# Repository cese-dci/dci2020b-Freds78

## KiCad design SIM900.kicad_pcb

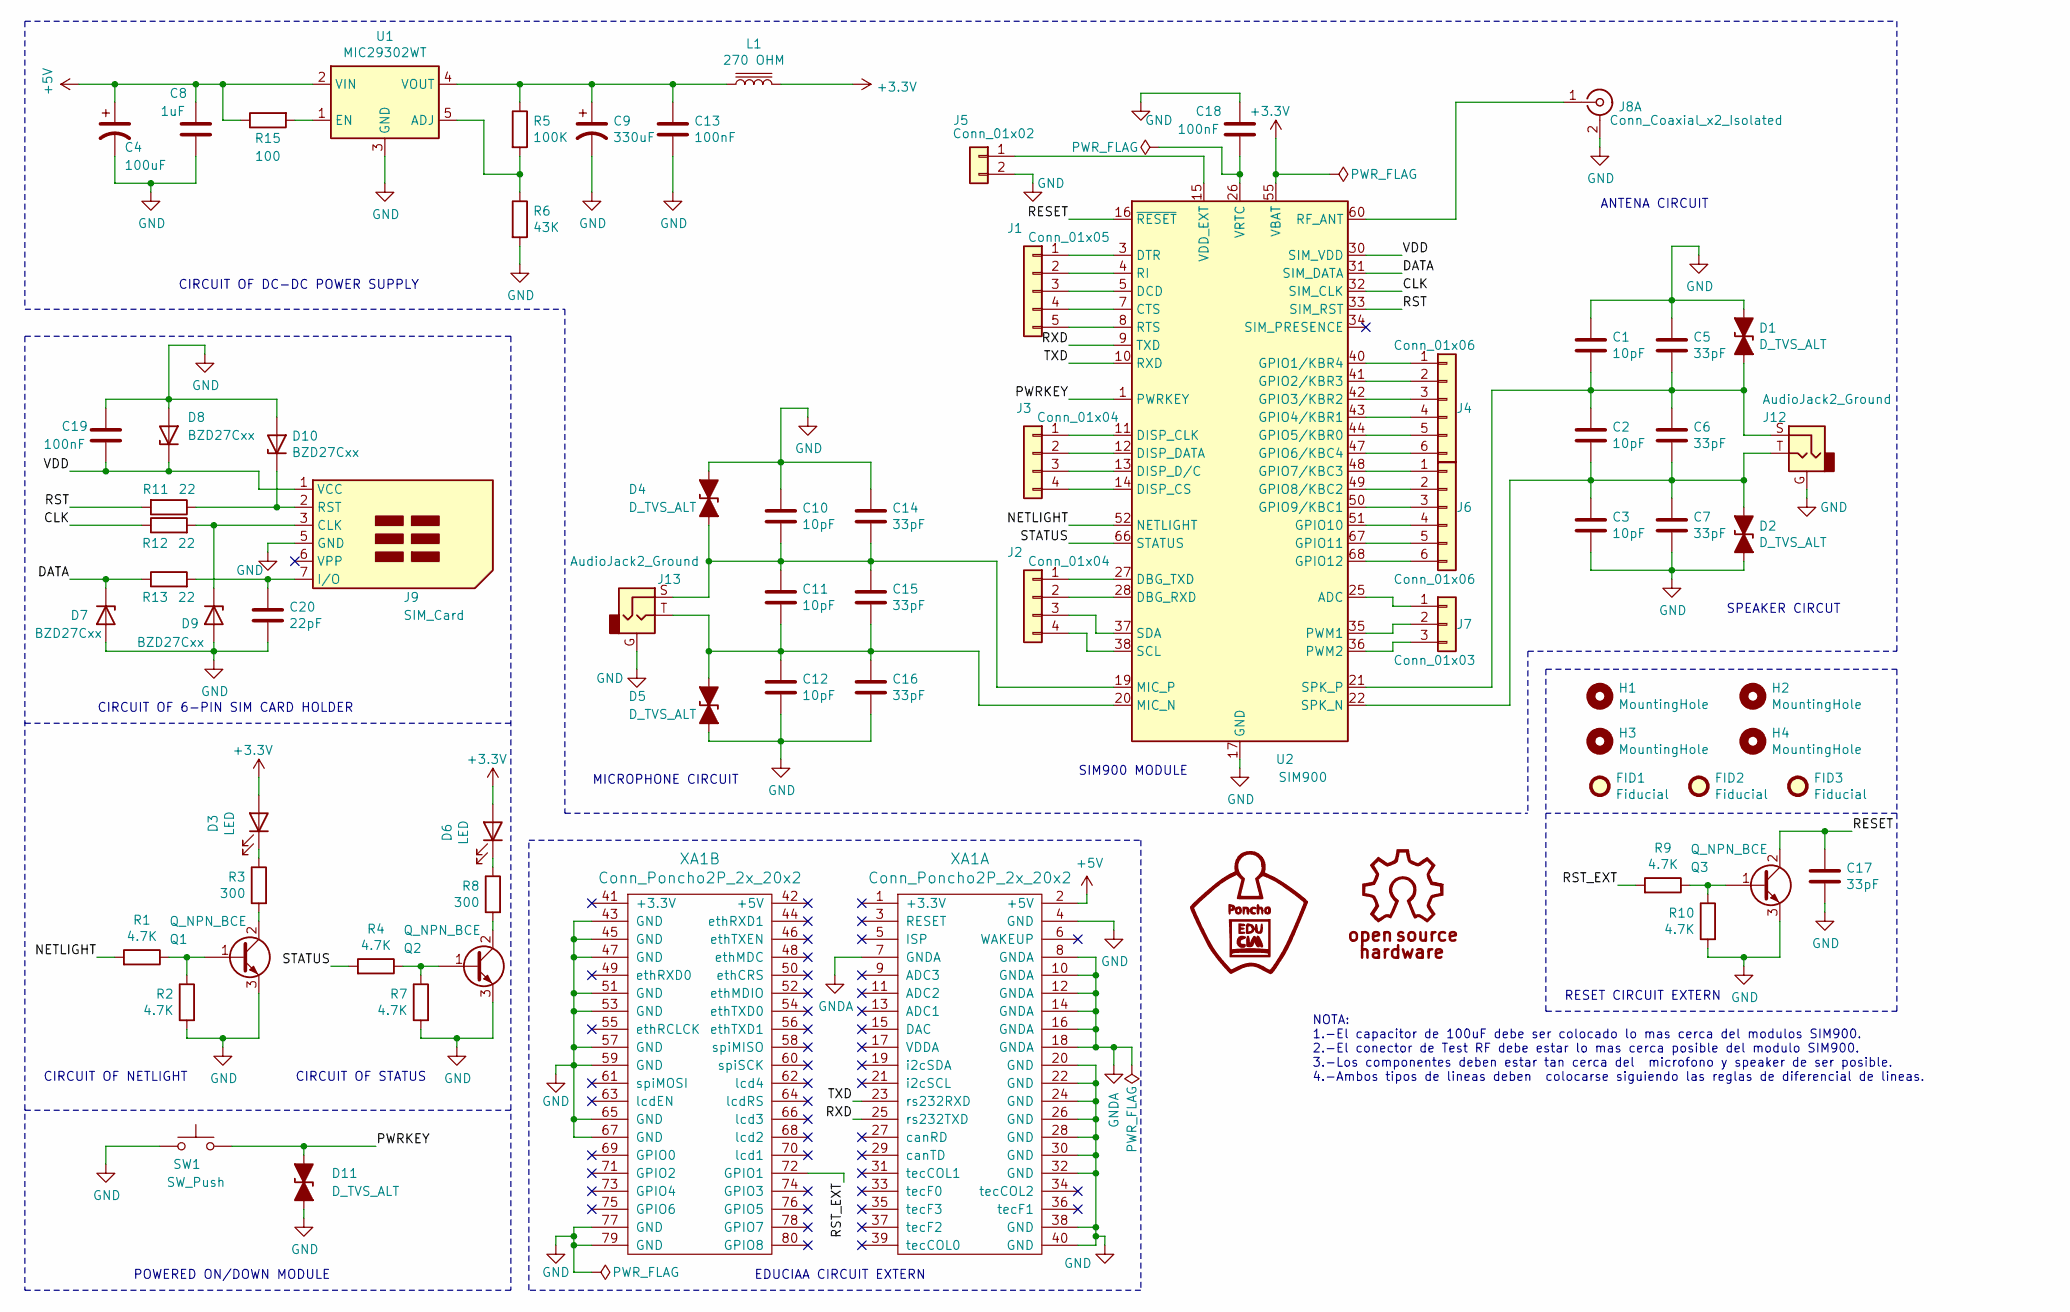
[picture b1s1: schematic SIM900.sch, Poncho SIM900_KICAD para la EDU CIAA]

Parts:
C1, C2, C3, C10, C11, C12: 10pF; C_0805_2012Metric; Digikey 399-17617-2-ND
C4: 100uF; C_1206_3216Metric; Digikey 718-2364-6-ND
C5, C6, C7, C14, C15, C16, C17: 33pF; C_0805_2012Metric; Digikey 399-17617-2-ND
C8: 1uF; C_0805_2012Metric; Digikey 399-17617-2-ND
C9: 330uF; C_2312_2020Metric_Pad3.2x6.0mm_HandSolder
C13, C18, C19: 100nF; C_0805_2012Metric; Digikey 399-17617-2-ND
C20: 22pF; C_0805_2012Metric; Digikey 399-17617-2-ND
D1, D2, D4, D11: D_TVS_ALT; D_SMA_Handsoldering; Digikey SMAJ22CAQ-13-FDITR-ND
D3: LED; LED_0805_2012Metric; Digikey 2460-L171L-QYC-TR-ND
D5: D_TVS_ALT; D_SMA_Handsoldering
D6: LED; LED_0805_2012Metric; Digikey 2460-L171L-LICTR-ND
D7: BZD27Cxx; D_SMF
D8, D9, D10: BZD27Cxx; D_SMF; Digikey BZD27C16P-E3-08GITR-ND
FID1, FID2, FID3: Fiducial; Fiducial_0.75mm_Mask2.25mm
H1, H2, H3, H4: MountingHole; MountingHole_2.5mm_Pad
J1: Conn_01x05; PinHeader_1x05_P2.54mm_Vertical; Digikey S6103-ND
J2, J3: Conn_01x04; PinHeader_1x04_P2.54mm_Vertical; Digikey S9009E-04-ND
J4, J6: Conn_01x06; PinHeader_1x06_P2.54mm_Vertical; Digikey S7004-ND
J5: Conn_01x02; JST_EH_S2B-EH_1x02_P2.50mm_Horizontal
J7: Conn_01x03; PinHeader_1x03_P2.54mm_Vertical; Digikey S9008E-03-ND
J8: Conn_Coaxial_x2_Isolated; SMA_Amphenol_901-144_Vertical; Digikey 2057-RF2-49B-T-00-50-G-HDW-ND
J9: SIM_Card; microSD_HC_Hirose_DM3D-SF; Digikey WM6698DKR-ND
J12, J13: AudioJack2_Ground; Jack_3.5mm_CUI_SJ-3523-SMT_Horizontal; Digikey CP-SJ2-35813B-SMT-DKR-ND
L1: 270 OHM; L_0805_2012Metric; Digikey 490-LQW2BAS6N0J00LDKR-ND
Q1, Q2, Q3: Q_NPN_BCE; SOT-23W; Digikey BC848BHZGT116DKR-ND
R1, R2, R4, R7, R10: 4.7K; R_0805_2012Metric_Pad1.15x1.40mm_HandSolder; Digikey 73L3R10JTR-ND
R3, R8: 300; R_0805_2012Metric_Pad1.15x1.40mm_HandSolder; Digikey 73L3R10JTR-ND
R5: 100K; R_0805_2012Metric_Pad1.15x1.40mm_HandSolder; Digikey 73L3R10JTR-ND
R6: 43K; R_0805_2012Metric_Pad1.15x1.40mm_HandSolder; Digikey 73L3R10JTR-ND
R9: 4.7K; R_0805_2012Metric_Pad1.15x1.40mm_HandSolder
R11, R12, R13: 22; R_0805_2012Metric_Pad1.15x1.40mm_HandSolder; Digikey 73L3R10JTR-ND
R15: 100; R_0805_2012Metric_Pad1.15x1.40mm_HandSolder; Digikey 73L3R10JTR-ND
SW1: SW_Push; SW_Tactile_SPST_Angled_PTS645Vx31-2LFS
U1: MIC29302WT; TO-263-5_TabPin3; Digikey 576-1124-ND
U2: SIM900; SIMCom_SIM900; Digikey 1597-1231-ND
XA1: Conn_Poncho2P_2x_20x2; Conn_Poncho_Chico

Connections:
+3V3: D3.2 (A), D6.2 (A), L1.2, U2.55 (VBAT), U2.56 (VBAT), U2.57 (VBAT)
+5V: C4.1, C8.1, R15.1, U1.2 (VIN), XA1.2 (+5V)
/CLK: R12.1, U2.32 (SIM_CLK)
/DATA: D7.1 (K), R13.1, U2.31 (SIM_DATA)
/NETLIGHT: R1.2, U2.52 (NETLIGHT)
/PWRKEY: D11.1 (A1), SW1.2, U2.1 (PWRKEY)
/RESET: C17.1, Q3.2 (C), U2.16 (~RESET~)
/RST: R11.2, U2.33 (SIM_RST)
/RST_EXT: R9.2, XA1.72 (GPIO1)
/RXD: U2.9 (TXD), XA1.25 (rs232TXD)
/STATUS: R4.2, U2.66 (STATUS)
/TXD: U2.10 (RXD), XA1.23 (rs232RXD)
/VDD: C19.1, D8.1 (K), J9.1 (VCC), U2.30 (SIM_VDD)
GND: C1.2, C3.2, C4.2, C5.2, C7.2, C8.2, C9.2, C10.2, C12.2, C13.2, C14.2, C16.2, C17.2, C18.2, C19.2, C20.2, D1.1 (A1), D2.2 (A2), D4.1 (A1), D5.2 (A2), D7.2 (A), D8.2 (A), D9.2 (A), D10.2 (A), D11.2 (A2), J5.2, J8.2 (Ext1), J9.5 (GND), J12.G, J13.G, Q1.3 (E), Q2.3 (E), Q3.3 (E), R2.2, R6.2, R7.2, R10.2, SW1.1, U1.3 (GND), U2.17 (GND), U2.18 (GND), U2.29 (GND), U2.39 (GND), U2.45 (GND), U2.46 (GND), U2.53 (GND), U2.54 (GND), U2.58 (GND), U2.59 (GND), U2.61 (GND), U2.62 (GND), U2.63 (GND), U2.64 (GND), U2.65 (GND), XA1.4 (GND), XA1.20 (GND), XA1.22 (GND), XA1.24 (GND), XA1.26 (GND), XA1.28 (GND), XA1.30 (GND), XA1.32 (GND), XA1.38 (GND), XA1.40 (GND), XA1.43 (GND), XA1.45 (GND), XA1.47 (GND), XA1.51 (GND), XA1.53 (GND), XA1.57 (GND), XA1.59 (GND), XA1.65 (GND), XA1.67 (GND), XA1.77 (GND), XA1.79 (GND)
GNDA: XA1.7 (GNDA), XA1.8 (GNDA), XA1.10 (GNDA), XA1.12 (GNDA), XA1.14 (GNDA), XA1.16 (GNDA), XA1.18 (GNDA)
unnamed: C1.1, C2.2, C5.1, C6.2, D1.2 (A2), J12.S, U2.21 (SPK_P)
unnamed: C2.1, C3.1, C6.1, C7.1, D2.1 (A1), J12.T, U2.22 (SPK_N)
unnamed: C10.1, C11.2, C14.1, C15.2, D4.2 (A2), J13.S, U2.19 (MIC_P)
unnamed: C11.1, C12.1, C15.1, C16.1, D5.1 (A1), J13.T, U2.20 (MIC_N)
unnamed: C9.1, C13.1, L1.1, R5.1, U1.4 (VOUT)
unnamed: C18.1, U2.26 (VRTC)
unnamed: C20.1, J9.7 (I/O), R13.2
unnamed: D3.1 (K), R3.1
unnamed: D6.1 (K), R8.1
unnamed: D9.1 (K), J9.3 (CLK), R12.2
unnamed: D10.1 (K), J9.2 (RST), R11.1
unnamed: J1.1, U2.3 (DTR)
unnamed: J1.2, U2.4 (RI)
unnamed: J1.3, U2.5 (DCD)
unnamed: J1.4, U2.7 (CTS)
unnamed: J1.5, U2.8 (RTS)
unnamed: J2.1, U2.27 (DBG_TXD)
unnamed: J2.2, U2.28 (DBG_RXD)
unnamed: J2.3, U2.37 (SDA)
unnamed: J2.4, U2.38 (SCL)
unnamed: J3.1, U2.11 (DISP_CLK)
unnamed: J3.2, U2.12 (DISP_DATA)
unnamed: J3.3, U2.13 (DISP_D/C)
unnamed: J3.4, U2.14 (DISP_CS)
unnamed: J4.1, U2.40 (GPIO1/KBR4)
unnamed: J4.2, U2.41 (GPIO2/KBR3)
unnamed: J4.3, U2.42 (GPIO3/KBR2)
unnamed: J4.4, U2.43 (GPIO4/KBR1)
unnamed: J4.5, U2.44 (GPIO5/KBR0)
unnamed: J4.6, U2.47 (GPIO6/KBC4)
unnamed: J5.1, U2.15 (VDD_EXT)
unnamed: J6.1, U2.48 (GPIO7/KBC3)
unnamed: J6.2, U2.49 (GPIO8/KBC2)
unnamed: J6.3, U2.50 (GPIO9/KBC1)
unnamed: J6.4, U2.51 (GPIO10)
unnamed: J6.5, U2.67 (GPIO11)
unnamed: J6.6, U2.68 (GPIO12)
unnamed: J7.1, U2.25 (ADC)
unnamed: J7.2, U2.35 (PWM1)
unnamed: J7.3, U2.36 (PWM2)
unnamed: J8.1 (In1), U2.60 (RF_ANT)
unnamed: Q1.1 (B), R1.1, R2.1
unnamed: Q1.2 (C), R3.2
unnamed: Q2.1 (B), R4.1, R7.1
unnamed: Q2.2 (C), R8.2
unnamed: Q3.1 (B), R9.1, R10.1
unnamed: R5.2, R6.1, U1.5 (ADJ)
unnamed: R15.2, U1.1 (EN)

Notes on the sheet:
CIRCUIT OF DC-DC POWER SUPPLY
POWERED ON/DOWN MODULE
SPEAKER CIRCUT
MICROPHONE CIRCUIT
CIRCUIT OF 6-PIN SIM CARD HOLDER
CIRCUIT OF NETLIGHT
CIRCUIT OF STATUS
RESET CIRCUIT EXTERN
SIM900 MODULE
NOTA: 1.-El capacitor de 100uF debe ser colocado lo mas cerca del modulos SIM900. 2.-El conector de Test RF debe estar lo mas cerca posible del modulo SIM900. 3.-Los componentes deben estar tan cerca del microfono y speaker de ser posible. 4.-Ambos tipos de lineas deben colocarse siguiendo las regl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
EDUCIAA CIRCUIT EXTERN
ANTENA CIRCUIT

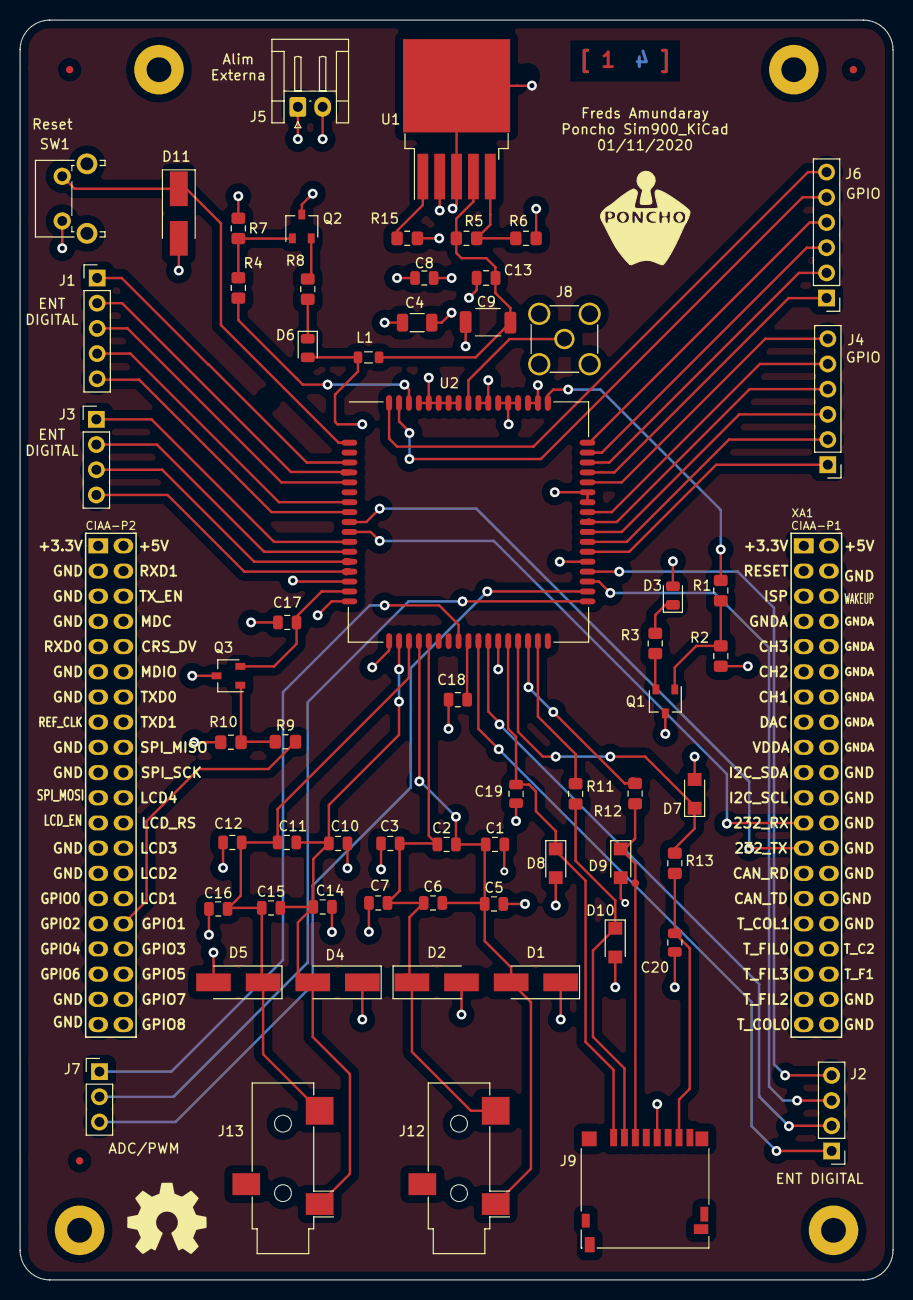
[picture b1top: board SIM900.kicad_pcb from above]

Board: 4 copper layers, 88.0 x 127.0 mm, 72 parts (0 on the bottom side), 63 nets.

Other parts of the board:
G101: Logo_OSHWA

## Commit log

2020-09-25 Esquematicos SIM900
2020-10-05 Se realizaron las modificaciones de los comentarios hechos en la planilla de revision
2020-10-09 Se incluyo el poncho de la EDU CIAA y se ordenaron los componentes dentro de ella
2020-10-12 Se ordeno mejor los componentes y se redujo la planilla de la EDU CIAA
2020-10-15 Se completo el PCB y se corrigieron la mayoria de las observaciones del profeor
2020-10-16 Se mejoro el conexionado en el PCB
2020-10-22 Se realizaron los cambios a los comentarios hechos por el profesor
2020-11-04 Correccion de los comentarios realizados por el profesor al PCB
2020-11-06 se corrigio algunas cosas faltantes de las observaciones realizadas
